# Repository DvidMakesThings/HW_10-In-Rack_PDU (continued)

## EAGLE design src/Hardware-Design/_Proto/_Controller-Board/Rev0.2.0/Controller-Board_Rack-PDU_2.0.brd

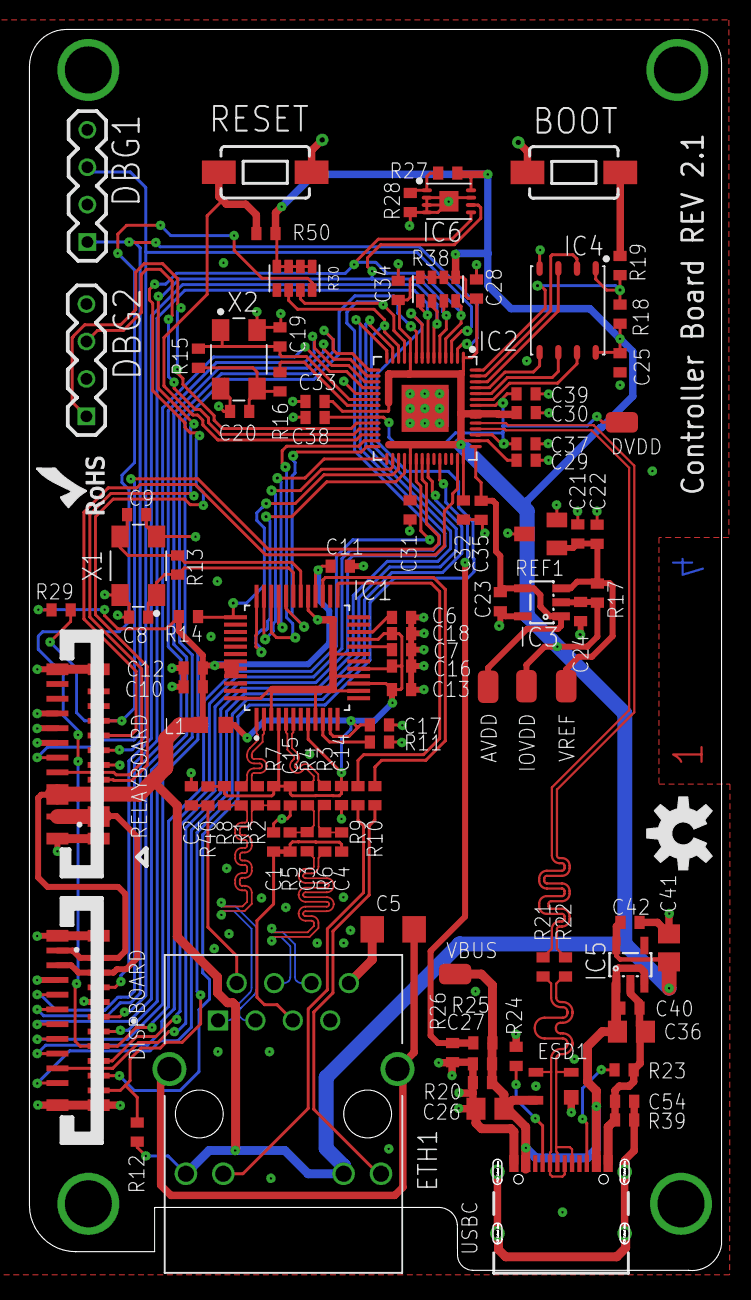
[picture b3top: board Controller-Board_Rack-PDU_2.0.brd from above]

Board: 4 copper layers, 47.0 x 84.3 mm, 104 parts (0 on the bottom side), 78 nets.

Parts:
AVDD: TP
BOOT: RS032G05A3SM-SPST-MOMENTARY-SWSMD-1101NE; TACTILE-SWITCH-1101NE
C1, C6, C10, C11, C12, C13, C14, C15, C16, C17, C18, C22, C23, C24, C25, C28, C29, C30, C31, C32, C33, C34, C35, C37, C38, C39: 100nF; C0402
C2: 22nF; C0402
C3, C4: 6.8nF; C0402
C5: C1206C102KGRACTM; C1206
C7: 4.7uF; C0402
C8, C9: 18pF; C0402
C19, C20: 15pF; C0402
C21: 1uF; C0402
C26, C36, C41: 10uF; 0805
C27, C40, C42: 100nF; 0402
C54: 4.7nF; 0402
DBG1, DBG2: 1X4
DISPBOARD: 687320124422
DVDD: TP
ESD1: SP0503BAHTG-ES; SOT143
ETH1: SI-60118-F; RJ45-CAT5
IC1: W5500; LQFP48
IC2: RP2040; QFN40P700X700X100-57T510
IC3: MCP6001R; SOT23-5
IC4: W25Q128JVPIQ; SON127P600X500X75-8N
IC5: MIC5504-3.3YM5-TR; SOT23-5
IC6: CAT24C512HU5IGT3; SON50P300X200X50-9T130X140N
IOVDD: TP
L1: BLM18EG221TN1D; 0603
R1, R2, R3, R4: 3.3R; 0402
R5, R6: 49.9R; C0402
R7, R8: 49.9R; 0402
R9, R10, R40: 470R; 0402
R11: 12.4K 1%; 0402
R12, R25, R26, R29, R50: 10K; 0402
R13, R39: 1M; 0402
R14, R17, R28: 4.7K; 0402
R15: 0R; 0402
R16, R19: 1K; 0402
R18: DNI; 0402
R20: 2.2K 1%; 0402
R21, R22: 27R; 0402
R23, R24: 5.1K; 0402
R27: NC; 0402
R30, R38: 4D03WGJ0332T5E; 742C083103JP
REF1: LM4040BXX; SOT23
RELAYBOARD: 687320124422
RESET: RS032G05A3SM-SPST-MOMENTARY-SWSMD-1101NE; TACTILE-SWITCH-1101NE
U$1: 4-LAYER
U$2: OSHW-LOGO-M
U$3: ROHS_LOGO_0.18_IN
USBC: USB-TYPE-C-018; 629722000214
VBUS: TP
VREF: TP
X1: XC53M4-25.000-F18NJDTL; OSCCC500X320X130
X2: K5A1200015304P; OSCCC500X320X130

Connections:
!ACT: IC1.27, R10.1
!LINK: IC1.25, R9.1
!QSPI_SS: IC2.56, IC4.1, R18.1, R19.2
!W5500_CS: IC1.32, IC2.28
!W5500_INT: IC1.36, IC2.32
!W5500_RST: IC1.37, IC2.31, R14.1
+1V1: C37.1, C38.1, C39.1, DVDD.TP, IC2.23, IC2.45, IC2.50
+3V3: C10.1, C11.1, C12.1, C24.1, C25.1, C28.1, C29.1, C30.1, C31.1, C32.1, C33.1, C34.1, C41.1, C42.1, DISPBOARD.1, DISPBOARD.2, ETH1.9, ETH1.11, IC1.28, IC1.43, IC1.44, IC1.45, IC2.1, IC2.10, IC2.22, IC2.33, IC2.42, IC2.44, IC2.48, IC2.49, IC3.2, IC4.8, IC5.5, IC6.8, IOVDD.TP, L1.1, R12.2, R14.2, R17.2, R18.2, R27.2, R29.2, R30.1, R30.2, R30.3, R30.4, R38.5, R38.6, R38.7, R38.8, R50.1, RELAYBOARD.4, RELAYBOARD.5, RELAYBOARD.6
+3V3_A: C13.1, C14.1, C15.1, C16.1, C17.1, C18.1, IC1.4, IC1.8, IC1.11, IC1.15, IC1.17, IC1.21, L1.2, R7.2, R8.2, R40.2
+5V: DISPBOARD.3, DISPBOARD.4, RELAYBOARD.1, RELAYBOARD.2, RELAYBOARD.3
+12V_MEA: IC2.41, RELAYBOARD.13
ADC_V_USB: IC2.38, R25.2, R26.1
AVDD: AVDD.TP, C23.1, C35.1, IC2.43, IC3.1, IC3.4
CC1: R24.1, USBC.A5
CC2: R23.1, USBC.B5
CHASSIS: C5.2, ETH1.S1, ETH1.S2
DP_N: ESD1.3, R21.1, USBC.A7, USBC.B7
DP_P: ESD1.2, R22.1, USBC.A6, USBC.B6
GND: BOOT.2, C1.2, C2.2, C5.1, C6.2, C7.2, C8.2, C9.2, C10.2, C11.2, C12.2, C13.2, C14.2, C15.2, C16.2, C17.2, C18.2, C19.2, C20.2, C21.2, C22.2, C23.2, C24.2, C25.2, C26.2, C27.2, C28.2, C29.2, C30.2, C31.2, C32.2, C33.2, C34.2, C35.2, C36.2, C37.2, C38.2, C39.2, C40.2, C41.2, C42.2, C54.2, DBG1.2, DBG1.4, DBG2.2, DBG2.4, DISPBOARD.5, DISPBOARD.8, DISPBOARD.Z1, DISPBOARD.Z2, DISPBOARD.Z3, DISPBOARD.Z4, ESD1.1, ETH1.8, IC1.3, IC1.9, IC1.14, IC1.16, IC1.19, IC1.29, IC1.48, IC2.19, IC2.57, IC3.5, IC4.4, IC5.2, IC6.2, IC6.3, IC6.4, IC6.7, IC6.9, R11.1, R20.2, R23.2, R24.2, R26.2, R28.1, R39.2, REF1.2, REF1.3, RELAYBOARD.9, RELAYBOARD.12, RELAYBOARD.14, RELAYBOARD.16, RELAYBOARD.Z1, RELAYBOARD.Z2, RELAYBOARD.Z3, RELAYBOARD.Z4, RESET.1, USBC.A1, USBC.A12, USBC.B1, USBC.B12, X1.2, X1.4, X2.2, X2.4
I2C0_SCL: DISPBOARD.7, IC2.7, R38.1
I2C0_SDA: DISPBOARD.6, IC2.6, R38.2
I2C1_SCL: IC2.5, IC6.6, R38.3, RELAYBOARD.8
I2C1_SDA: IC2.4, IC6.5, R38.4, RELAYBOARD.7
KEY_0: DISPBOARD.12, IC2.15
KEY_1: DISPBOARD.11, IC2.16
KEY_2: DISPBOARD.10, IC2.17
KEY_3: DISPBOARD.9, IC2.18
LCD_BL: DISPBOARD.13, IC2.9
LCD_CS: DISPBOARD.19, IC2.12, R30.6
LCD_DC: DISPBOARD.18, IC2.8
LCD_MISO: DISPBOARD.15, IC2.11, R30.7
LCD_MOSI: DISPBOARD.16, IC2.14
LCD_RES: DISPBOARD.14, IC2.34, R30.8
LCD_SCLK: DISPBOARD.17, IC2.13
MCP_DSP_RST: DISPBOARD.20, IC2.36, R12.1
MCP_REL_RST: IC2.35, R29.1, RELAYBOARD.15
unnamed: IC1.10, R11.2
unnamed: ETH1.10, R9.2
unnamed: ETH1.12, R10.2
unnamed: C6.1, IC1.22
unnamed: C7.1, IC1.20
unnamed: C9.1, IC1.30, R13.1, X1.3
unnamed: C20.1, R15.2, R16.1, X2.3
unnamed: IC2.26, R50.2, RESET.2
unnamed: IC6.1, R27.1, R28.2
QSPI_SCLK: IC2.52, IC4.6
QSPI_SD0: IC2.53, IC4.5
QSPI_SD1: IC2.55, IC4.2
QSPI_SD2: IC2.54, IC4.3
QSPI_SD3: IC2.51, IC4.7
RCT: C1.1, ETH1.5, R5.1, R6.1
RDC_RD_N: C3.1, R4.2, R5.2
RDC_RD_P: C4.1, R3.2, R6.2
RD_N: C3.2, ETH1.6
RD_P: C4.2, ETH1.4
RP_XI: C19.1, IC2.20, R15.1, X2.1
RP_XO: IC2.21, R16.2
RX_RD_N: IC1.5, R4.1
RX_RD_P: IC1.6, R3.1
SWCLK: DBG2.1, IC2.24
SWDIO: DBG2.3, IC2.25
TCT: C2.1, ETH1.2, R40.1
TD_N: ETH1.3, R1.2, R8.1
TD_P: ETH1.1, R2.2, R7.1
TX_TD_N: IC1.1, R1.1
TX_TD_P: IC1.2, R2.1
UART0_RX: DBG1.1, IC2.2, RELAYBOARD.10
UART0_TX: DBG1.3, IC2.3, RELAYBOARD.11
USB_BOOT: BOOT.1, R19.1
USB_DP_N: IC2.46, R21.2
USB_DP_P: IC2.47, R22.2
USB_SHIELD: C54.1, R39.1, USBC.S1, USBC.S2, USBC.S3, USBC.S4
VBUS: C26.1, C27.1, C36.1, C40.1, ESD1.4, IC5.1, IC5.3, R20.1, R25.1, USBC.A4, USBC.A9, USBC.B4, USBC.B9, VBUS.TP
VREF: C21.1, C22.1, IC3.3, R17.1, REF1.1, VREF.TP
W5500_MISO: IC1.34, IC2.27
W5500_MOSI: IC1.35, IC2.30
W5500_SCK: IC1.33, IC2.29
XO: C8.1, IC1.31, R13.2, X1.1

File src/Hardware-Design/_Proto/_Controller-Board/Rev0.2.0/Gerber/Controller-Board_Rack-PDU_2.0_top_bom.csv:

Comment,Designator,Footprint,LCSC Part #
0R,R15,0402,
1K,R16 R19,0402,
1M,R13 R39,0402,
1uF,C21,C0402,
2.2K 1%,R20,0402,
3.3R,R1 R2 R3 R4,0402,
4.7K,R14 R17 R27 R28,0402,
4.7nF,C54,0402,
4.7uF,C7,C0402,
4D03WGJ0332T5E,R38,742C083103JP,
5.1K,R23 R24,0402,
6.8nF,C3 C4,C0402,
10K,R25 R26 R50,0402,
10uF,C26 C36 C41,0805,
12.4K 1%,R11,0402,
15pF,C19 C20,C0402,
18pF,C8 C9,C0402,
22nF,C2,C0402,
27R,R21 R22,0402,
49.9R,R5 R6,C0402,
49.9R,R7 R8,0402,
100nF,C1 C6 C10 C11 C12 C13 C14 C15 C16 C17 C18 C22 C23 C24 C25,C0402,
100nF,C27,0402,
100nF,C28 C29 C30 C31 C32 C33 C34 C35 C37 C38 C39,C0402,
100nF,C40 C42,0402,
470R,R9 R10 R40,0402,
430182043816,BOOT RESET,430182043816,
687320124422,DISPBOARD RELAYBOARD,687320124422,
BLM18EG221TN1D,L1,0603,
C1206C102KGRACTM,C5,C1206,
CAT24C256HU4IGT3,IC6,SON50P300X200X50-9T130X140N,
DNI,R18,0402,
K5A1200015304P,X2,OSCCC500X320X130,
LM4040BXX,REF1,SOT23,
MCP6001R,IC3,SOT23-5,
MIC5504-3.3YM5-TR,IC5,SOT23-5,
RP2040,IC2,QFN40P700X700X100-57T510,
SP0503BAHTG-ES,ESD1,SOT143,
TP,AVDD DVDD IOVDD VBUS VREF,TP,
USB-TYPE-C-018,USBC,629722000214,
W25Q128JVPIQ,IC4,SON127P600X500X75-8N,
W5500,IC1,LQFP48,
XC53M4-25.000-F18NJDTL,X1,OSCCC500X320X130,
